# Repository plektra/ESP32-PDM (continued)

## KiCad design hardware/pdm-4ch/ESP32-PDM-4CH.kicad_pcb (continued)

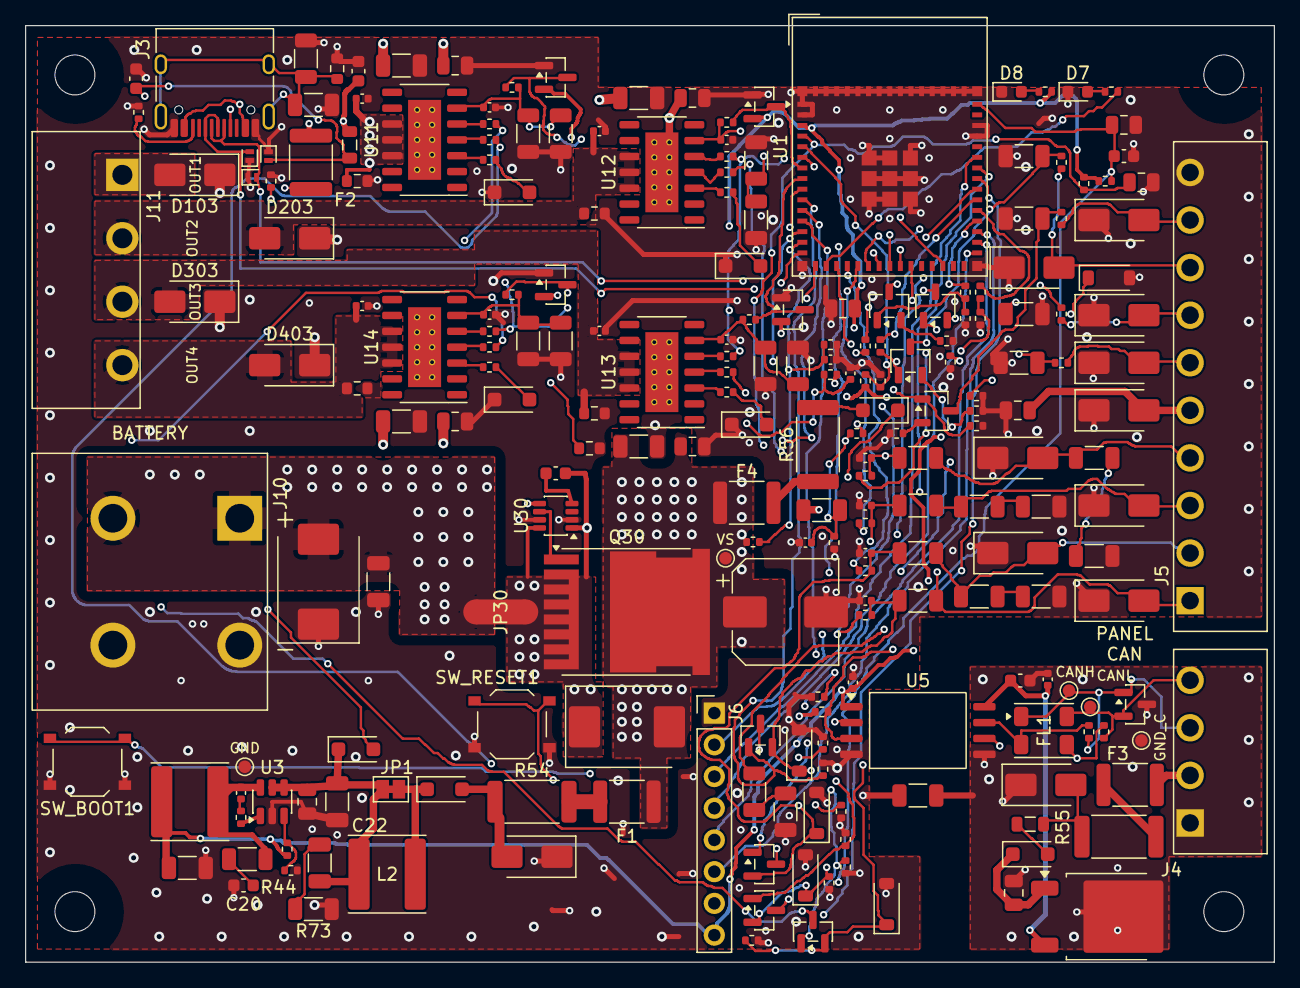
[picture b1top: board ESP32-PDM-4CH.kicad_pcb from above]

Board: 4 copper layers, 100.0 x 75.0 mm, 231 parts (0 on the bottom side), 130 nets.

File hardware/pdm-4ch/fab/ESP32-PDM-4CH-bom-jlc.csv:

Comment,Designator,Footprint,JLCPCB Part #
2.2uF/100V,"C1,C3,C30,C104,C204,C304,C404",C_1206_3216Metric,C170101
0.1uF,"C2,C10,C11,C60,C61",C_0402_1005Metric,C307331
1.0uF/50V,"C4,C6,C12,C32",C_0603_1608Metric,C15849
4.7uF/16V,C5,C_0603_1608Metric,C19666
100nF,"C7,C9,C19,C54,C103,C203,C303,C403",C_0805_2012Metric,C28233
22uF,C8,C_0805_2012Metric,C45783
1uF/50V,C13,C_0805_2012Metric,C28323
470nF,"C14,C15,C16,C17,C21",C_0402_1005Metric,C47339
1nF/2kV,"C18,C50,C51,C52,C53",C_1206_3216Metric,C9196
100uF/63V,C31,CP_Elec_8x10,C487384
100pF,"C101,C201,C301,C401",C_0402_1005Metric,C1546
10nF,"C102,C202,C302,C402",C_0402_1005Metric,C15195
SMAJ30CA,"D1,D16,D17,D18,D19,D50,D51,D52,D53,D54",D_SMA,C19077548
DSK16,"D2,D3,D11,D55,D101,D201,D301,D401",D_SOD-123F,C22466351
H5VL10B,"D4,D5,D6",D_SOD-882,C7420372
KT-0603R red,"D7,D8",LED_0603_1608Metric,C2286
PESD2CAN,D9,SOT-23,C2687131
SMAJ18CA,D10,D_SMA,C19077539
BAT54C,"D12,D13,D14,D15",SOT-23,C22466350
BZT52C3V3,"D20,D21,D22,D23,D24",D_SOD-123,C19077396
SMCJ30CA,D30,D_SMC,C19077607
SMDJ40CA,D31,D_SMC,C42371557
BAT54S,"D102,D202,D302,D402",SOT-23,C7420333
mSMD050-60V,"F1,F2,F3,F4",Fuse_1812_4532Metric,C70113
GZ2012D601TF,"FB1,FB2",L_0805_2012Metric,C1017
TYPE-C-31-M-12,J3,USB_C_Receptacle_HRO_TYPE-C-31-M-12,C165948
SWPA6045S8R2MT,L1,L_Sunlord_SWPA6045S,C96963
MMBT5551,"Q3,Q4,Q5,Q6",SOT-23-3,C2145
AGM601LL,Q30,Infineon_PG-HSOF-8-1,C5464765
2.2k,"R1,R2,R5,R6,R59,R67",R_0402_1005Metric,C25879
2k,"R3,R4,R7,R8,R45,R46,R47,R48",R_1206_3216Metric,C17944
68k,R9,R_0402_1005Metric,C36871
22k,"R10,R61",R_0402_1005Metric,C25768
5.1k,"R11,R12",R_0402_1005Metric,C25905
1M,R13,R_1206_3216Metric,C17927
10k,"R15,R16,R17,R21,R24,R27,R29,R30,R31,R32,R33,R42,R58,R62,R70,R101,R102,R104,R201,R202,R204,R301,R302,R304,R401,R402,R404",R_0402_1005Metric,C25744
1k,"R18,R20,R23,R26",R_0402_1005Metric,C11702
100,"R19,R22,R25,R28",R_0402_1005Metric,C25076
10k,"R34,R35,R36,R37,R49",R_1206_3216Metric,C17902
4.7k,"R38,R39,R40,R41,R57",R_0402_1005Metric,C25900
0,"R43,R71,R72",R_0402_1005Metric,C17168
470,"R50,R51,R52,R53",R_0402_1005Metric,C25117
200m,"R54,R55,R56",R_2512_6332Metric,C7420022
220k,R60,R_0402_1005Metric,C25767
1k,"R103,R107,R203,R207,R303,R307,R403,R407",R_1206_3216Metric,C844867
22,"R105,R205,R305,R405",R_0402_1005Metric,C25092
SW_Push,"SW_BOOT1,SW_RESET1",SW_Push_1P1T_XKB_TS-1187A,C318884
10k B3380,TH1,R_0603_1608Metric,C52155402
ESP32-S3-MINI-1,U1,ESP32-S2-MINI-1,C2913206
LMR51610YDBVR,U3,SOT-23-6,C22427220
CA-IS3050G,U5,SOIC-8_7.5x5.85mm_P1.27mm,C528763
L78M05ABDT,U6,TO-252-2,C58069
BTT6050-1ERA,"U11,U12,U13,U14",Infineon_PG-TDSO-14_ThermalVias,C534868
LM74502H-Q1,U30,TI_DDF0008A,C5219203

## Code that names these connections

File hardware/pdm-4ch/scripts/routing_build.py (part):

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SIG_LAYERS = ('F.Cu', 'In2.Cu', 'B.Cu')       # no signal on In1.Cu (EMC rule 3)
HV = {'VS', '/VBAT_IN'}
P6 = {'Net-(D2-K)', 'Net-(D3-K)', 'Net-(F1-Pad2)', 'Net-(F4-Pad2)', '/Analog interface/SW_SUPPLY', 'Net-(F3-Pad1)',
      'Net-(J4-Pin_2)', 'Net-(D11-K)', 'Net-(C22-Pad2)', '/OUT1', '/OUT2', '/OUT3', '/OUT4', '/VBAT_FL'}
P4 = {'Net-(F2-Pad1)', 'Net-(C4-Pad1)', 'Net-(D3-A)', 'Net-(U5-VCC2)', 'Net-(Q30-G)', 'Net-(U30-VCAP)'}
BUCK_TOP = {'Net-(U3-SW)', 'Net-(U3-CB)'}      # buck SW/CB on F.Cu only (no via in the loop)
# Power pours whose router keep-out bars tracks only (decision 172, Q-0070): foreign-net vias may pass through; the
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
